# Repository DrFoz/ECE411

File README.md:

# ECE411
Repository for ECE 411 practicum project documentation

Project overview

This project encompasses the hardware and software design of a haptic feedback compass
to assist an individual with landbased navigation.
Applications could include hiking, hunting, or as additional aid for the visually impaired.
Direction will be determined with the use of a digital magnometer and microprocessor. 
Mode Select and direction select will be set with the use of a momentary switch mounted to 
the case. Feedback will be generated using micro dc vibrator motor, to indicate mode and
direction selected, as well as to indicate a deviation from desired direction. During 
operation Haptic feedback intensity will be preportional to the deviation of desired 
direction of travel. Device will be powered by a lithium polymer pouch cell that is 
removable and rechargeable via external charger.

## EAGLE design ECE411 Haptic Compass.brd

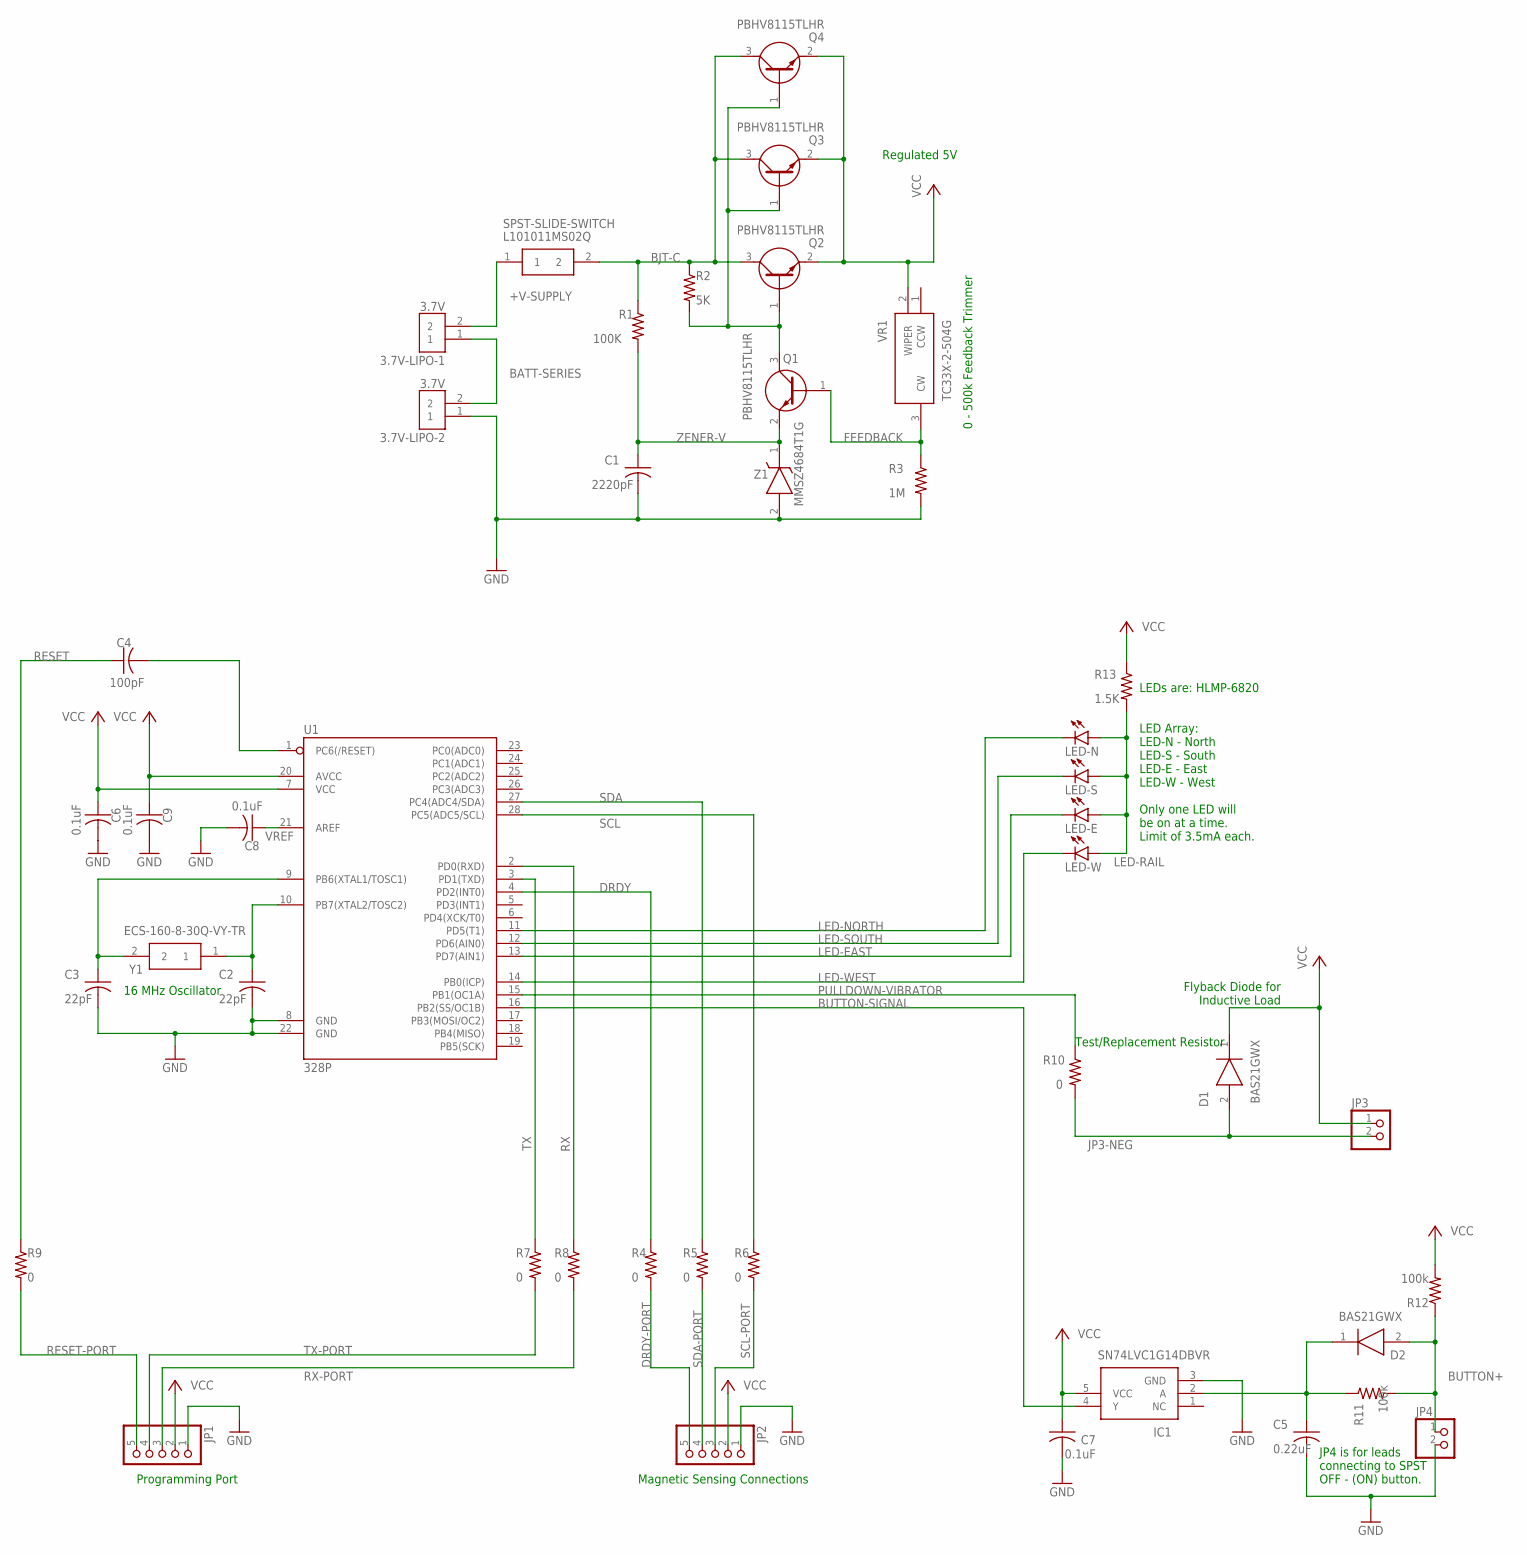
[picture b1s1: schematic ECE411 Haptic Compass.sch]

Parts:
3.7V-LIPO-1, 3.7V-LIPO-2: 3.7V; JST_S2B-PH-K-S(LF)(SN)
C1: 2220pF; C0805
C2, C3: 22pF; C0805
C4: 100pF; C0805
C5: 0.22uF; C0805
C6, C7, C8, C9: 0.1uF; C0805
D1, D2: BAS21GWX; SOD3616X130N
IC1: SN74LVC1G14DBVR; SOT95P280X145-5N
JP1, JP2: PINHD-1X5; 1X05
JP3, JP4: PINHD-1X2; 1X02
LED-E: LED5MM
LED-N: LED5MM
LED-S: LED5MM
LED-W: LED5MM
Q1, Q2, Q3, Q4: PBHV8115TLHR; SOT95P230X110-3N
R1: 100K; R0805
R2: 5K; R0805
R3: 1M; R0805
R4, R5, R6, R7, R8, R9, R10: 0; R0805
R11, R12: 100k; R0805
R13: 1.5K; R0805
SPST-SLIDE-SWITCH: L101011MS02Q; CKC5106-ND
U1: 328P; DIP28
VR1: TC33X-2-504G; TC33X-2_1
Y1: ECS-160-8-30Q-VY-TR; ECS80830QVSTR
Z1: MMSZ4684T1G; SOD3716X135N

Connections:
+V-SUPPLY: 3.7V-LIPO-1.2, SPST-SLIDE-SWITCH.1
BATT-SERIES: 3.7V-LIPO-1.1, 3.7V-LIPO-2.2
BJT-C: Q2.3 (C), Q3.3 (C), Q4.3 (C), R1.1, R2.1, SPST-SLIDE-SWITCH.2
BUTTON+: D2.2 (A), JP4.1, R11.2, R12.1
BUTTON-SIGNAL: IC1.4 (Y), U1.16 (PB2(SS/OC1B))
DRDY: R4.1, U1.4 (PD2(INT0))
DRDY-PORT: JP2.5, R4.2
FEEDBACK: Q1.1 (B), R3.1, VR1.3 (CW)
GND: 3.7V-LIPO-2.1, C1.2, C2.2, C3.2, C5.2, C6.2, C7.2, C8.2, C9.2, IC1.3 (GND), JP1.1, JP2.1, JP4.2, R3.2, U1.8 (GND), U1.22 (GND), Z1.2 (A)
JP3-NEG: D1.2 (A), JP3.2, R10.2
LED-EAST: LED-E.K (C), U1.13 (PD7(AIN1))
LED-NORTH: LED-N.K (C), U1.11 (PD5(T1))
LED-RAIL: LED-E.A, LED-N.A, LED-S.A, LED-W.A, R13.2
LED-SOUTH: LED-S.K (C), U1.12 (PD6(AIN0))
LED-WEST: LED-W.K (C), U1.14 (PB0(ICP))
unnamed: C4.2, U1.1 (PC6(/RESET))
unnamed: C5.1, D2.1 (K), IC1.2 (A), R11.1
unnamed: C2.1, U1.10 (PB7(XTAL2/TOSC2)), Y1.1
unnamed: C3.1, U1.9 (PB6(XTAL1/TOSC1)), Y1.2
unnamed: Q1.3 (C), Q2.1 (B), Q3.1 (B), Q4.1 (B), R2.2
PULLDOWN-VIBRATOR: R10.1, U1.15 (PB1(OC1A))
RESET: C4.1, R9.1
RESET-PORT: JP1.5, R9.2
RX: R8.1, U1.2 (PD0(RXD))
RX-PORT: JP1.3, R8.2
SCL: R6.1, U1.28 (PC5(ADC5/SCL))
SCL-PORT: JP2.3, R6.2
SDA: R5.1, U1.27 (PC4(ADC4/SDA))
SDA-PORT: JP2.4, R5.2
TX: R7.1, U1.3 (PD1(TXD))
TX-PORT: JP1.4, R7.2
VCC: C6.1, C7.1, C9.1, D1.1 (K), IC1.5 (VCC), JP1.2, JP2.2, JP3.1, Q2.2 (E), Q3.2 (E), Q4.2 (E), R12.2, R13.1, U1.7 (VCC), U1.20 (AVCC), VR1.2 (WIPER)
VREF: C8.1, U1.21 (AREF)
ZENER-V: C1.1, Q1.2 (E), R1.2, Z1.1 (K)

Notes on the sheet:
16 MHz Oscillator
Regulated 5V
0 - 500k Feedback Trimmer
Programming Port
Magnetic Sensing Connections
Flyback Diode for Inductive Load
Test/Replacement Resistor
JP4 is for leads connecting to SPST OFF - (ON) button.
LEDs are: HLMP-6820 LED Array: LED-N - North LED-S - South LED-E - East LED-W - West Only one LED will be on at a time. Limit of 3.5mA each.

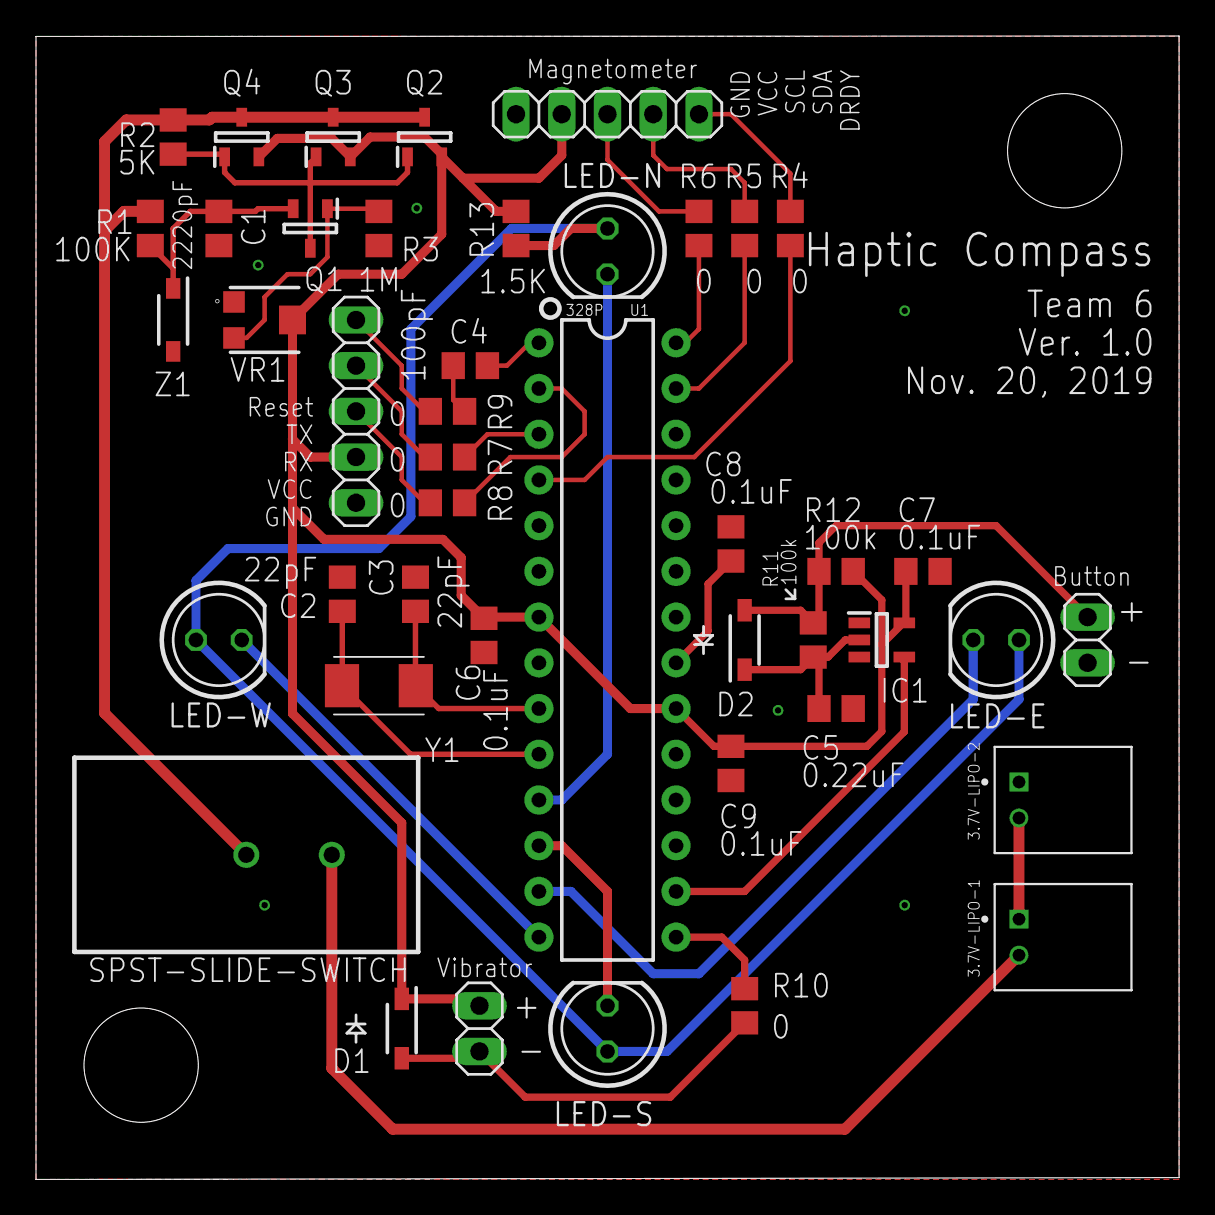
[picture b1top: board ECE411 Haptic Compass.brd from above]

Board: 2 copper layers, 63.5 x 63.5 mm, 44 parts (0 on the bottom side), 34 nets.

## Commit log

2019-10-15 Create designLog.txt
    Design Log first commit. Created log and added first entry.
2019-10-15 Created BOM, Created Eagle file, modified design log
    Created BOM and populated components used to date, created empty eagle project to establish path, updated design log
2019-10-15 Updated README.MD to include project overview
2019-10-16 Create practicumIdeas.txt
    Three possible practicum project ideas
2019-10-16 Update designLog.txt
    build log
2019-10-17 Update gy273_test.ino
    test code for physical connections only
2019-10-20 initial test
2019-10-20 Updated practicumIdeas.txt
    Added chosen project statement
2019-10-21 Create TF_failedattempt.sch
    I clearly need to get experience in eagle
2019-10-21 Create HMC588L_atmega328p_motortest.ino
    Simple program to test motor functionality
2019-10-21 Update eagle.epf
    still a failure
2019-10-23 Create QMC5883L_atmega328p.ino
    Code for testing compass modules with QMC5883L chipset
2019-10-23 Update QMC5883L_atmega328p.ino
    Added code to test motor and magnetometer accuracy
2019-10-23 Update QMC5883L_atmega328p.ino
    Playing with direction accuracy
2019-10-24 Create compass_pseudo_code.txt
    Very basic pseudo code. Not all cases shown for logic.
2019-10-24 Update compass_pseudo_code.txt
    added assumptions comment
2019-10-24 Update QMC5883L_atmega328p.ino
    shortened delay for testing
2019-10-24 Haptic Compass Schematic
    Creation of Power Supply and implementation of libraries and the Magnetic Sensing module.
2019-10-26 Update QMC5883L_atmega328p.ino
    code in progress for testing hardware
2019-10-30 Added Reworked Power Supply for 5V
2019-10-31 Added all modules and I/O
    Note that the Magnetic Sensing Module is there as a placeholder. The I/O pins are at the bottom for the actual device in creation.
2019-10-31 Minor Fixes (ERC)
    Fixed junction errors and Vcc connection errors.
2019-10-31 images folder created
    Created images folder uploaded prototype image
2019-10-31 added prototype image
2019-11-07 Create practicum_ECE_411.pod
    Project schedule for practicum
2019-11-07 Matts Update to the POD
    Will need overlook and insight from the rest of the team in the continuation of the POD file.
2019-11-07 Re-update due to Bugs in Program
2019-11-07 Update practicum_ECE_411.pod
    Hacked apart Matts good work, looking for approval
2019-11-07 Update to Practicum Project Schedule
    Added OSHPARK and Timing
2019-11-07 Practicum Program Schedule with Critical Path
    The critical path for the Consolidation doesn't light up as red when it should. Unsure why?
2019-11-07 Create practicum_schedule_ECE411.pod
    Created alternate due to crappy software task sheduling bug
2019-11-07 Update practicum_schedule_ECE411.pod
    Need to add schedule updates
2019-11-07 Update practicum_schedule_ECE411.pod
    messing with schedule updates
2019-11-07 Update practicum_schedule_ECE411.pod
    final commit
2019-11-07 Increased PCB Fabrication to 12 day turnaround
    Final update
2019-11-07 Bugfixes to Update
    Fixing the timeline to match durations and dates
2019-11-14 Completed Schematic
    Board layout will be completed next.
2019-11-14 BOM and Haptic Compass Schematic Update
    Included all components and revamped connector for batteries for an in-stock component.
2019-11-14 Renaming for T6
2019-11-14 Created Board Layout for Haptic Compass
    Ground planes are left to be created. More will be done to it as revisions this week go through.
2019-11-16 Layout Finish - Ground Plane Added
2019-11-19 Placement of switch on top
2019-11-20 Included 1uF Capacitor next to Vcc for the uPC
2019-11-21 Board Final
    Added AVCC, AGND, and VCC bypass capacitors and connected AGND and GND.
2019-11-21 Feedback Notes & Final Board
2019-12-11 Create haptic_feedback.ino
    Ruben code first Commit

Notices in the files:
parts and their libraries:
SparkFun-IC-Microcontroller: Licensing: Creative Commons ShareAlike 4.0 International - https://creativecommons.org/licenses/by-sa/4.0
